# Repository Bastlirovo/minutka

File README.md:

# minutka
HW &amp; SW for Minutka project

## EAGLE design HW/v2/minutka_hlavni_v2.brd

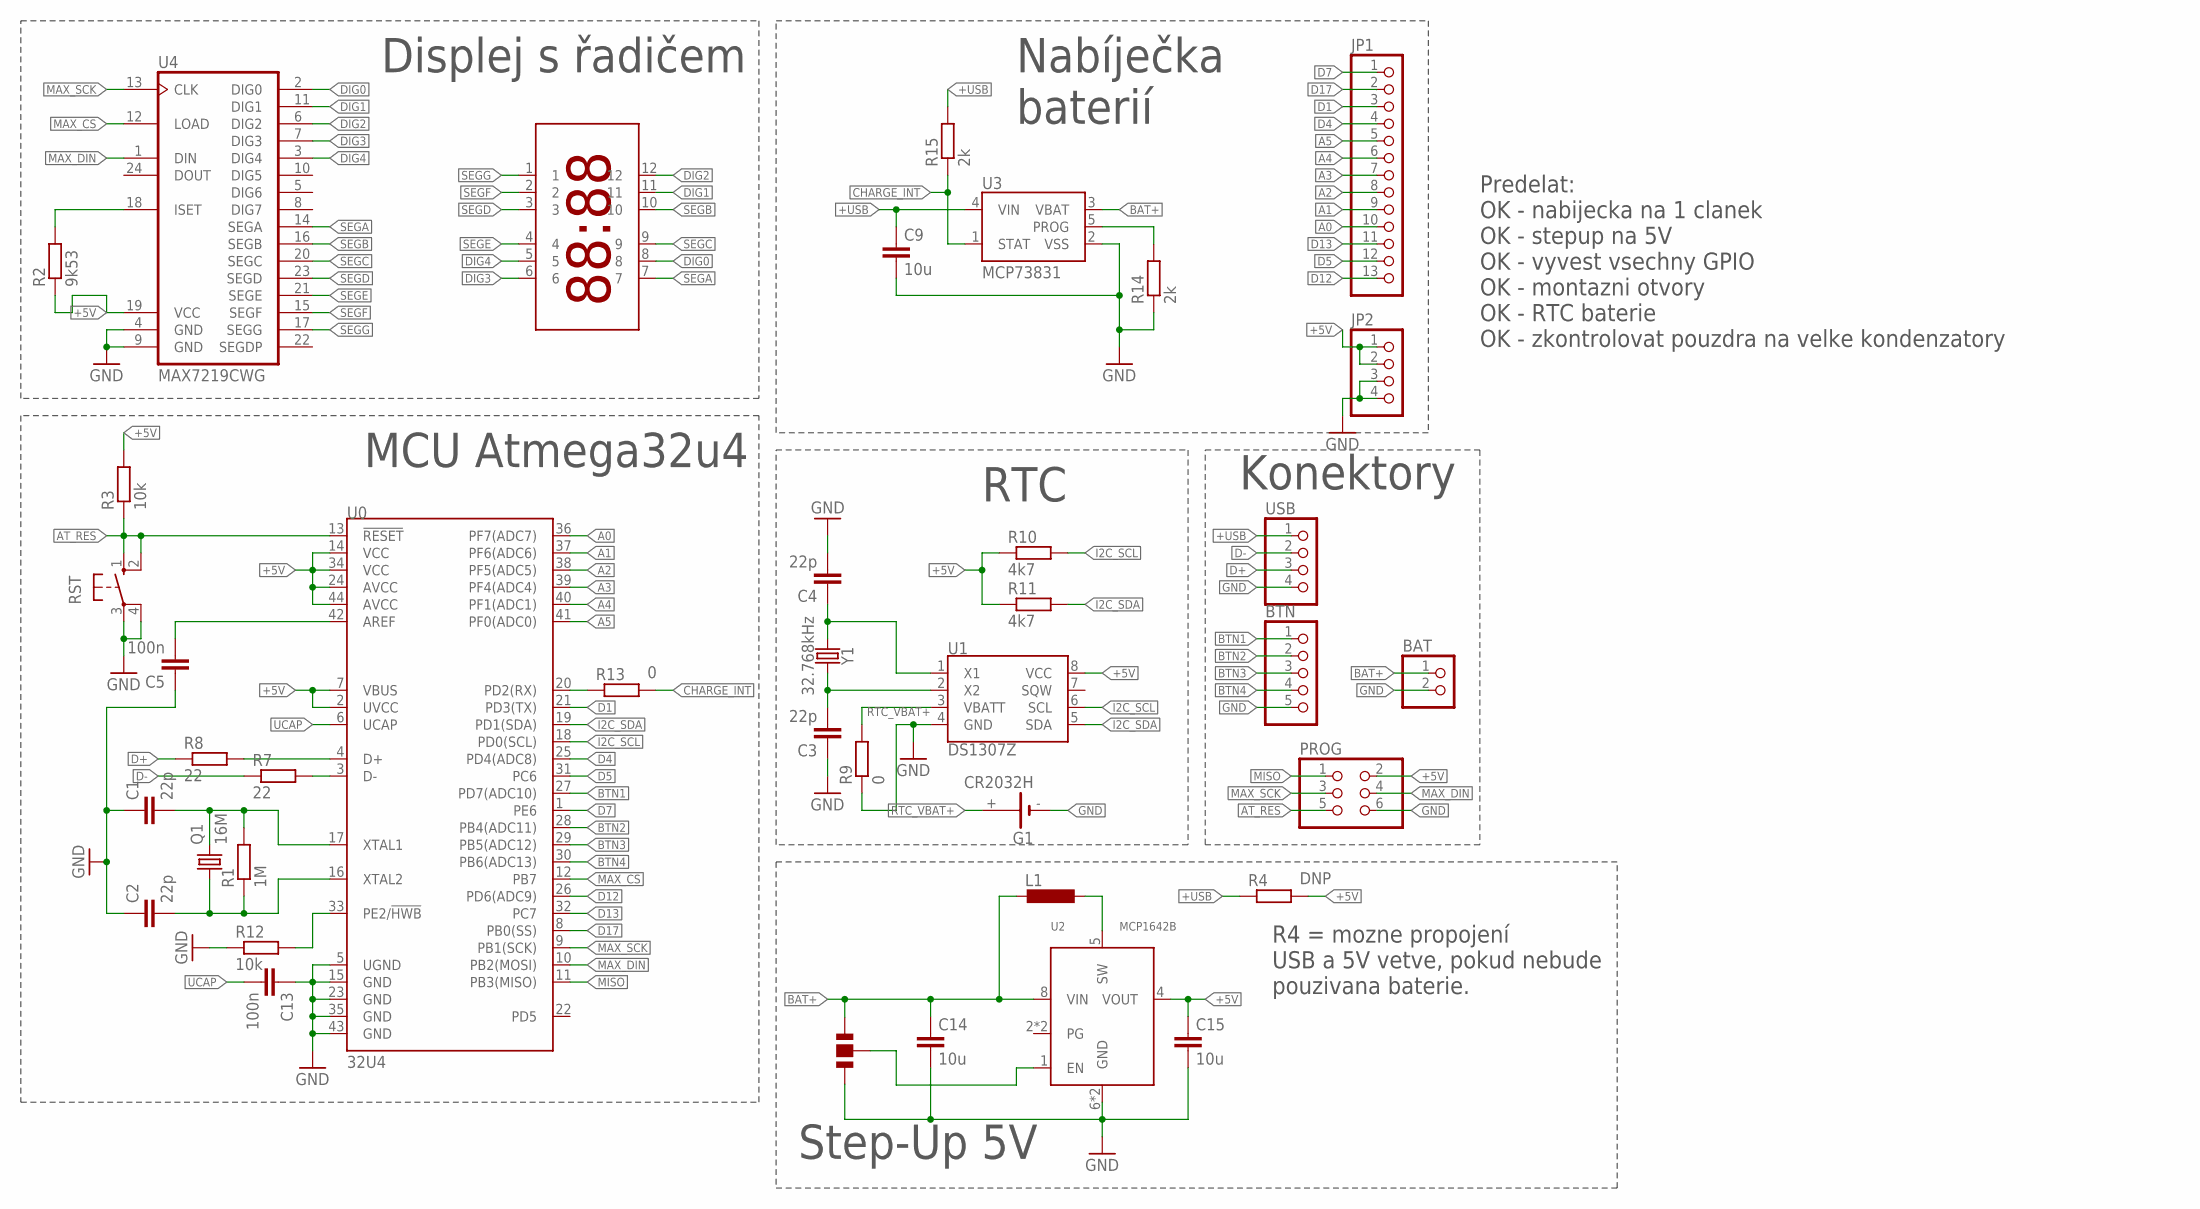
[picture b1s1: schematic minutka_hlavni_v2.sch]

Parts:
BAT: PINHD-1X2; 1X02
BTN: PINHD-1X5; 1X05
C1, C2, C3, C4: 22p; C0603
C5, C13: 100n; C0603
C9, C14, C15: 10u; C1206
G1: CR2032H
JP1: PINHD-1X13; 1X13
JP2: PINHD-1X4; 1X04
L1: L-EUL4532P; L4532P
PROG: PINHD-2X3; 2X03
Q1: 16M; HC49UP
R1: 1M; R0603
R2: 9k53; R0603
R3, R12: 10k; R0603
R4: DNP; R0603
R7, R8: 22; R0603
R9, R13: 0; R0603
R10, R11: 4k7; R0603
R14, R15: 2k; R0603
RST: 10-XX; B3F-10XX
U0: 32U4; TQFP44
U1: DS1307Z; SO08-0.15
U2: MCP1642B; MSOP8
U3: MCP73831; SOT95P290X120-5
U4: MAX7219CWG; SO24L
U$2: KW4-8828AVB
U$7: JUMPER; 2-WAY
USB: PINHD-1X4; 1X04
Y1: 32.768kHz; CRYSTAL-SMD-2X6-CYL

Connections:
+5V: C15.1, JP2.1, JP2.2, PROG.2, R2.1, R3.2, R4.2, R10.1, R11.1, U0.2 (UVCC), U0.7 (VBUS), U0.14 (VCC), U0.24 (AVCC), U0.34 (VCC), U0.44 (AVCC), U1.8 (VCC), U2.4 (VOUT), U4.19 (VCC)
+USB: C9.1, R4.1, R15.2, U3.4 (VIN), USB.1
A0: JP1.10, U0.36 (PF7(ADC7))
A1: JP1.9, U0.37 (PF6(ADC6))
A2: JP1.8, U0.38 (PF5(ADC5))
A3: JP1.7, U0.39 (PF4(ADC4))
A4: JP1.6, U0.40 (PF1(ADC1))
A5: JP1.5, U0.41 (PF0(ADC0))
AT_RES: PROG.5, R3.1, RST.1 (S), RST.2 (S1), U0.13 (!RESET)
BAT+: BAT.1, C14.1, L1.2, U2.8 (VIN), U3.3 (VBAT), U$7.P$2
BTN1: BTN.1, U0.27 (PD7(ADC10))
BTN2: BTN.2, U0.28 (PB4(ADC11))
BTN3: BTN.3, U0.29 (PB5(ADC12))
BTN4: BTN.4, U0.30 (PB6(ADC13))
CHARGE_INT: R13.2, R15.1, U3.1 (STAT)
D1: JP1.3, U0.21 (PD3(TX))
D4: JP1.4, U0.25 (PD4(ADC8))
D5: JP1.12, U0.31 (PC6)
D7: JP1.1, U0.1 (PE6)
D12: JP1.13, U0.26 (PD6(ADC9))
D13: JP1.11, U0.32 (PC7)
D17: JP1.2, U0.8 (PB0(SS))
D+: R8.1, USB.3
D-: R7.1, USB.2
DIG0: U4.2 (DIG0), U$2.8
DIG1: U4.11 (DIG1), U$2.11
DIG2: U4.6 (DIG2), U$2.12
DIG3: U4.7 (DIG3), U$2.6
DIG4: U4.3 (DIG4), U$2.5
GND: BAT.2, BTN.5, C1.1, C2.1, C3.1, C4.2, C5.1, C9.2, C13.1, C14.2, C15.2, G1.-, JP2.3, JP2.4, PROG.6, R9.1, R12.1, R14.1, RST.3, RST.4 (P1), U0.5 (UGND), U0.15 (GND), U0.23 (GND), U0.35 (GND), U0.43 (GND), U1.4 (GND), U2.6 (GND), U2.7 (GND), U3.2 (VSS), U4.4 (GND), U4.9 (GND), U$7.P$3, USB.4
I2C_SCL: R10.2, U0.18 (PD0(SCL)), U1.6 (SCL)
I2C_SDA: R11.2, U0.19 (PD1(SDA)), U1.5 (SDA)
MAX_CS: U0.12 (PB7), U4.12 (LOAD)
MAX_DIN: PROG.4, U0.10 (PB2(MOSI)), U4.1 (DIN)
MAX_SCK: PROG.3, U0.9 (PB1(SCK)), U4.13 (CLK)
MISO: PROG.1, U0.11 (PB3(MISO))
unnamed: C1.2, Q1.2, R1.2, U0.17 (XTAL1)
unnamed: C2.2, Q1.1, R1.1, U0.16 (XTAL2)
unnamed: C4.1, U1.1 (X1), Y1.X1 (1)
unnamed: C3.2, U1.2 (X2), Y1.X2 (2)
unnamed: R2.2, U4.18 (ISET)
unnamed: C5.2, U0.42 (AREF)
unnamed: R8.2, U0.4 (D+)
unnamed: R7.2, U0.3 (D-)
unnamed: R12.2, U0.33 (PE2/!HWB)
unnamed: R13.1, U0.20 (PD2(RX))
unnamed: R14.2, U3.5 (PROG)
unnamed: L1.1, U2.5 (SW)
unnamed: U2.1 (EN), U$7.P$1
RTC_VBAT+: G1.+, R9.2, U1.3 (VBATT)
SEGA: U4.14 (SEGA), U$2.7
SEGB: U4.16 (SEGB), U$2.10
SEGC: U4.20 (SEGC), U$2.9
SEGD: U4.23 (SEGD), U$2.3
SEGE: U4.21 (SEGE), U$2.4
SEGF: U4.15 (SEGF), U$2.2
SEGG: U4.17 (SEGG), U$2.1
UCAP: C13.2, U0.6 (UCAP)

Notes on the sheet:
Predelat: OK - nabijecka na 1 clanek OK - stepup na 5V OK - vyvest vsechny GPIO OK - montazni otvory OK - RTC baterie OK - zkontrolovat pouzdra na velke kondenzatory
Displej s řadičem
Nabíječka baterií
MCU Atmega32u4
RTC
Konektory
Step-Up 5V
R4 = mozne propojení USB a 5V vetve, pokud nebude pouzivana baterie.

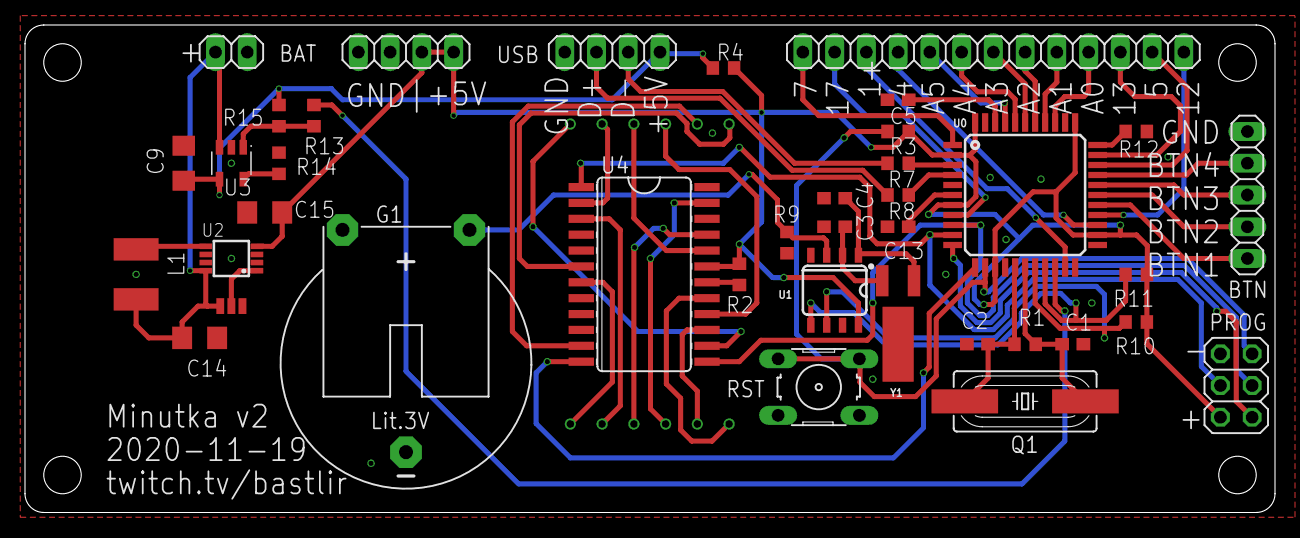
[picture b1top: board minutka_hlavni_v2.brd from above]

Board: 2 copper layers, 100.0 x 39.0 mm, 40 parts (1 on the bottom side), 58 nets.

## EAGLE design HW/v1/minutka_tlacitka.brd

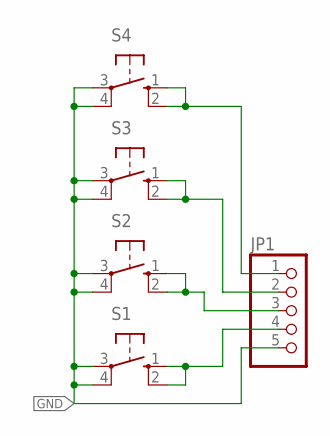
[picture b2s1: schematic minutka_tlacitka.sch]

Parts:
JP1: PINHD-1X5; 1X05
S1, S2, S3, S4: 40-XX; B3F-40XX

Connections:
GND: JP1.5, S1.3, S1.4 (P1), S2.3, S2.4 (P1), S3.3, S3.4 (P1), S4.3, S4.4 (P1)
unnamed: JP1.3, S2.1 (S), S2.2 (S1)
unnamed: JP1.1, S4.1 (S), S4.2 (S1)
unnamed: JP1.2, S3.1 (S), S3.2 (S1)
unnamed: JP1.4, S1.1 (S), S1.2 (S1)

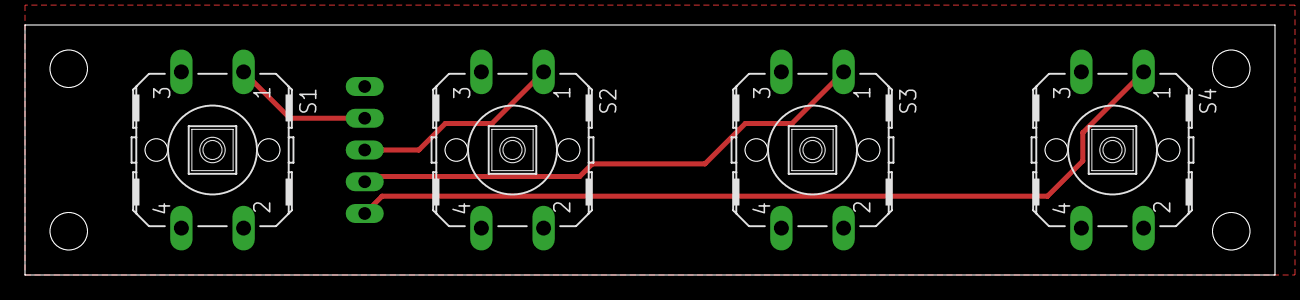
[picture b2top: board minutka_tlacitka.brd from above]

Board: 2 copper layers, 100.0 x 20.0 mm, 5 parts (1 on the bottom side), 5 nets.

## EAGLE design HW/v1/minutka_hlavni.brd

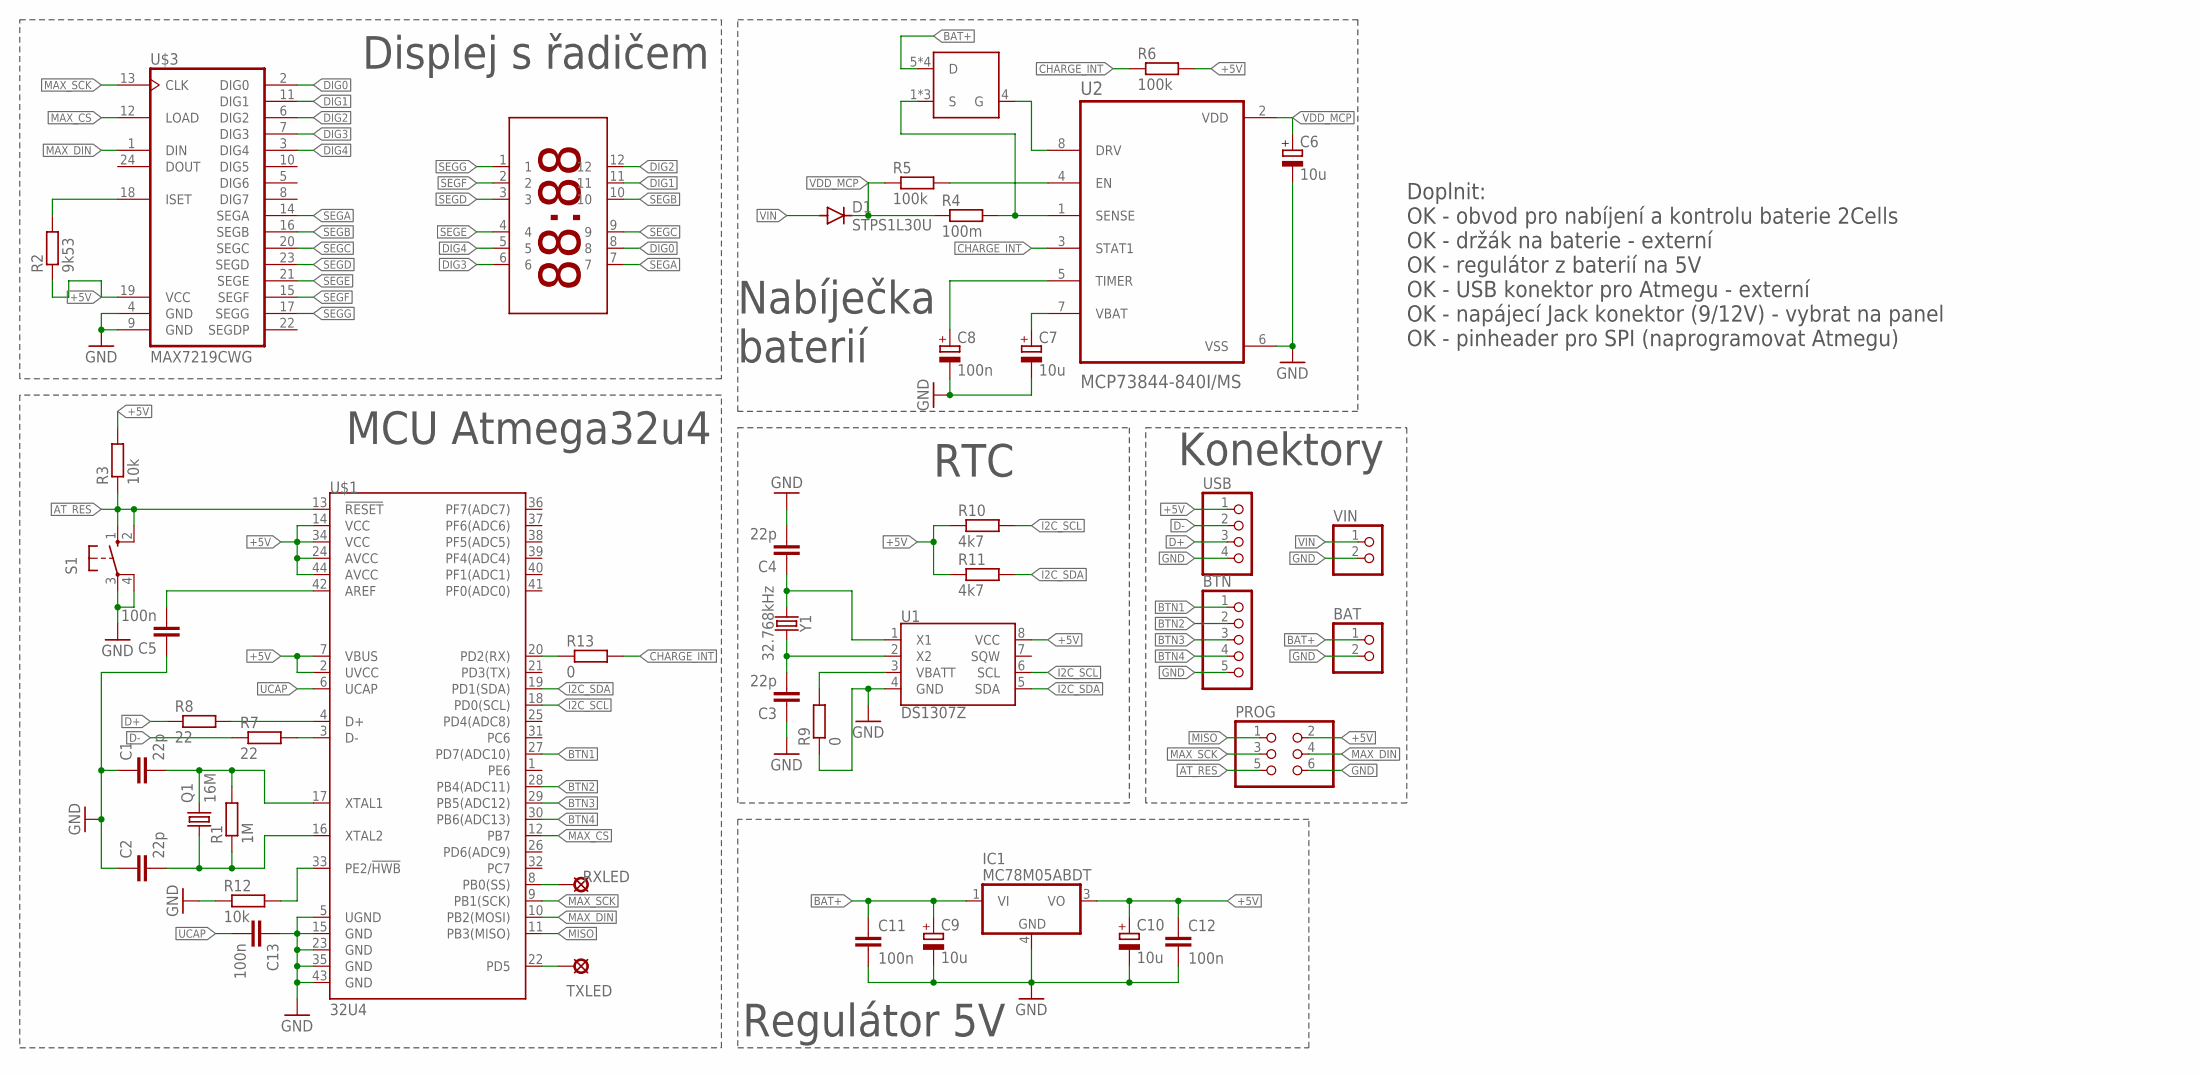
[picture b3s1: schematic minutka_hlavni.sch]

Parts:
BAT: PINHD-1X2; 1X02
BTN: PINHD-1X5; 1X05
C1, C2, C3, C4: 22p; C0603
C5, C11, C12, C13: 100n; C0603
C6, C7, C9, C10: 10u; 085CS_1AR
C8: 100n; 085CS_1AR
D1: STPS1L30U; DO214AA
IC1: MC78M05ABDT; DPACK_3
PROG: PINHD-2X3; 2X03
Q1: 16M; HC49UP
R1: 1M; R0603
R2: 9k53; R0603
R3, R12: 10k; R0603
R4: 100m; R0603
R5, R6: 100k; R0603
R7, R8: 22; R0603
R9, R13: 0; R0603
R10, R11: 4k7; R0603
RXLED: LSP13
S1: 10-XX; B3F-10XX
TXLED: LSP13
U1: DS1307Z; SO08-0.15
U2: MCP73844-840I/MS; SOP65P490X110-8N
U$1: 32U4; TQFP44
U$2: KW4-8828AVB
U$3: MAX7219CWG; SO24L
U$4: NDS8434; SO08
USB: PINHD-1X4; 1X04
VIN: PINHD-1X2; 1X02
Y1: 32.768kHz; CRYSTAL-SMD-2X6-CYL

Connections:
+5V: C10.+, C12.1, IC1.3 (VO), PROG.2, R2.1, R3.2, R6.2, R10.1, R11.1, U1.8 (VCC), U$1.2 (UVCC), U$1.7 (VBUS), U$1.14 (VCC), U$1.24 (AVCC), U$1.34 (VCC), U$1.44 (AVCC), U$3.19 (VCC), USB.1
AT_RES: PROG.5, R3.1, S1.1 (S), S1.2 (S1), U$1.13 (!RESET)
BAT+: BAT.1, C9.+, C11.1, IC1.1 (VI), U$4.5 (D), U$4.6 (D), U$4.7 (D), U$4.8 (D)
BTN1: BTN.1, U$1.27 (PD7(ADC10))
BTN2: BTN.2, U$1.28 (PB4(ADC11))
BTN3: BTN.3, U$1.29 (PB5(ADC12))
BTN4: BTN.4, U$1.30 (PB6(ADC13))
CHARGE_INT: R6.1, R13.2, U2.3 (STAT1)
D+: R8.1, USB.3
D-: R7.1, USB.2
DIG0: U$2.8, U$3.2 (DIG0)
DIG1: U$2.11, U$3.11 (DIG1)
DIG2: U$2.12, U$3.6 (DIG2)
DIG3: U$2.6, U$3.7 (DIG3)
DIG4: U$2.5, U$3.3 (DIG4)
GND: BAT.2, BTN.5, C1.1, C2.1, C3.1, C4.2, C5.1, C6.-, C7.-, C8.-, C9.-, C10.-, C11.2, C12.2, C13.1, IC1.4 (GND), PROG.6, R9.1, R12.1, S1.3, S1.4 (P1), U1.4 (GND), U2.6 (VSS), U$1.5 (UGND), U$1.15 (GND), U$1.23 (GND), U$1.35 (GND), U$1.43 (GND), U$3.4 (GND), U$3.9 (GND), USB.4, VIN.2
I2C_SCL: R10.2, U1.6 (SCL), U$1.18 (PD0(SCL))
I2C_SDA: R11.2, U1.5 (SDA), U$1.19 (PD1(SDA))
MAX_CS: U$1.12 (PB7), U$3.12 (LOAD)
MAX_DIN: PROG.4, U$1.10 (PB2(MOSI)), U$3.1 (DIN)
MAX_SCK: PROG.3, U$1.9 (PB1(SCK)), U$3.13 (CLK)
MISO: PROG.1, U$1.11 (PB3(MISO))
unnamed: C1.2, Q1.2, R1.2, U$1.17 (XTAL1)
unnamed: C2.2, Q1.1, R1.1, U$1.16 (XTAL2)
unnamed: C4.1, U1.1 (X1), Y1.X1 (1)
unnamed: C3.2, U1.2 (X2), Y1.X2 (2)
unnamed: U2.8 (DRV), U$4.4 (G)
unnamed: R4.2, U2.1 (SENSE), U$4.1 (S), U$4.2 (S), U$4.3 (S)
unnamed: R2.2, U$3.18 (ISET)
unnamed: C5.2, U$1.42 (AREF)
unnamed: C7.+, U2.7 (VBAT)
unnamed: R8.2, U$1.4 (D+)
unnamed: R7.2, U$1.3 (D-)
unnamed: C8.+, U2.5 (TIMER)
unnamed: R12.2, U$1.33 (PE2/!HWB)
unnamed: TXLED.MP, U$1.22 (PD5)
unnamed: R5.2, U2.4 (EN)
unnamed: RXLED.MP, U$1.8 (PB0(SS))
unnamed: R13.1, U$1.20 (PD2(RX))
RTC_VBAT+: R9.2, U1.3 (VBATT)
SEGA: U$2.7, U$3.14 (SEGA)
SEGB: U$2.10, U$3.16 (SEGB)
SEGC: U$2.9, U$3.20 (SEGC)
SEGD: U$2.3, U$3.23 (SEGD)
SEGE: U$2.4, U$3.21 (SEGE)
SEGF: U$2.2, U$3.15 (SEGF)
SEGG: U$2.1, U$3.17 (SEGG)
UCAP: C13.2, U$1.6 (UCAP)
VDD_MCP: C6.+, D1.C, R4.1, R5.1, U2.2 (VDD)
VIN: D1.A, VIN.1

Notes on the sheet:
Doplnit: OK - obvod pro nabíjení a kontrolu baterie 2Cells OK - držák na baterie - externí OK - regulátor z baterií na 5V OK - USB konektor pro Atmegu - externí OK - napájecí Jack konektor (9/12V) - vybrat na panel OK - pinheader pro SPI (naprogramovat Atmegu)
Displej s řadičem
Nabíječka baterií
MCU Atmega32u4
RTC
Konektory
Regulátor 5V

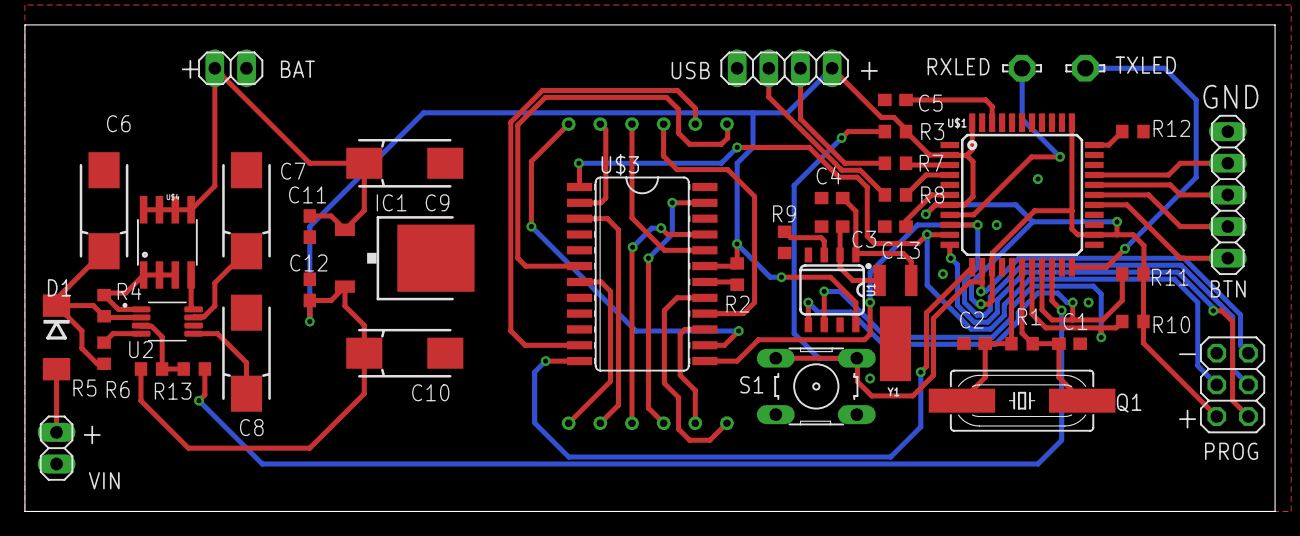
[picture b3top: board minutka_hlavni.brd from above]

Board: 2 copper layers, 100.3 x 39.0 mm, 44 parts (1 on the bottom side), 50 nets.

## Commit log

2020-10-10 HW v1 initial commit
2020-11-16 SW v1 Initial commit
2020-11-25 HW v2

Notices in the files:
parts and their libraries:
SparkFun-IC-Microcontroller: Licensing: Creative Commons ShareAlike 4.0 International - https://creativecommons.org/licenses/by-sa/4.0
